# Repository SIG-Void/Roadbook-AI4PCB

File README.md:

<h1 align="center"> Roadbook AI4PCB</h1>

Hardware engineers and researchers at SIGVoid maintain Roadbook AI4PCB. We study which parts of printed circuit board (PCB) design engineers can already hand over to AI. Here you can read research papers and engineering notes, or open a board file to see which connections a model got right. We are testing how well models read circuit diagrams, place parts, and connect them. We are also building training datasets from the steps engineers take to design a board and the checks they use to verify it.

<p align="center"><strong>English</strong> · <a href="README.zh-CN.md">中文</a> &nbsp; | &nbsp; <a href="https://sig-void.github.io/Roadbook-AI4PCB/">Explore the full roadbook ↗</a></p>

[Selected papers](#read-papers) · [Benchmarks and submissions](#read-benchmarks) · [Run a Harbor example](#read-harbor) · [Data and weights](#read-data) · [PCB engineering notes](#read-boards) · [Contribute](#read-contribute)

## Where can AI help with PCB design?

A schematic specifies which pins belong together. Placement sets the positions of the components. Routing adds the copper that connects their pads. Each paper below produces a different artifact you can inspect.

| Engineering question | Paper and project | What to inspect |
| --- | --- | --- |
| Can a model recover connections from a drawing? | [OmniSch paper](https://arxiv.org/abs/2604.00270) · [Examples and data](https://www.omnisch.com/) | Locate components and wires in a schematic. Compare the extracted connections with the netlist, which records which pins belong together. |
| Can a model draw an editable schematic from a requirement? | [SchGen paper](https://arxiv.org/abs/2605.30345) · [Code and examples](https://github.com/microsoft/SchGen) | Follow a 3.3 V regulator example from a written requirement to a KiCad schematic. Check the power pins in the result. |
| Will a proposed placement leave room for routing? | [RL_PCB paper](https://past.date-conference.com/proceedings-archive/2024/DATA/1040_pdf_upload.pdf) · [Test circuits](https://github.com/LukeVassallo/RL_PCB) | The model moves components. A router connects the resulting layout so the authors can compare placements by actual trace length. |
| Can an agent finish routing a board? | [PCBWorld environment](https://github.com/LGAI-Research/PCBWorld) · [PCBRouteAgent paper](https://arxiv.org/abs/2611.08175) | Starting from a placed board, the agent chooses the routing order and where to change layers. Inspect the final board in KiCad. |
| Can a model learn from routing actions? | [CADET paper](https://arxiv.org/abs/2611.16913) · [Generation and replay code](https://github.com/LGAI-Research/CADET) | Generate routing demonstrations, replay them in a fresh environment, and compare imitation learning with reinforcement learning. |

[Browse all papers by design stage →](https://sig-void.github.io/Roadbook-AI4PCB/research/papers/)

## Benchmarks and model submissions

**Agents’ Last Exam (ALE)** includes two KiCad tasks. The layout task starts with a schematic and asks for a routed board that fits a specified enclosure. The repair task asks the model to restore the footprint for U4 on a navigation switch board and export the manufacturing files.

SIGVoid ran each model once on each task in the ALE v1.1 Windows environment. The maximum score is 1 per task. Each ZIP contains the submitted files, a step-by-step action log, and the score.

| Model and reasoning setting | Board layout and routing | Navigation switch repair |
| --- | --- | --- |
| DeepSeek V4.1 Flash · max | **1** · [Submission and actions](https://sig-void.github.io/Roadbook-AI4PCB/assets/runs/ale-mini-deepseek.zip) | **0** · [Submission and actions](https://sig-void.github.io/Roadbook-AI4PCB/assets/runs/ale-navswitch-deepseek.zip) |
| Qwen4-Max-Preview · xhigh | **0** · [Submission and actions](https://sig-void.github.io/Roadbook-AI4PCB/assets/runs/ale-mini-qwen4.zip) | **0** · [Submission and actions](https://sig-void.github.io/Roadbook-AI4PCB/assets/runs/ale-navswitch-qwen4.zip) |

<p align="center"><br><sub>The DeepSeek layout submission, rendered from its KiCad file. Select the board to open the source.</sub></p>

Why did both repair submissions score zero? Both models fixed U4. DeepSeek omitted the required report formats and netlist. Qwen used different export names and omitted the required drill directory. Both submissions failed the required-file check. [Inspect the requirements and results](https://sig-void.github.io/Roadbook-AI4PCB/research/benchmarks/#ale-navswitch)

**What do the other benchmarks measure?**

- **OmniLayout tests placement.** A model supplies component positions, rotations, and board sides. The evaluator checks overlaps and boundaries, then tries to route the board. GPT-5.5 passed 15.23% of cases on its first submission with the base input and 42.83% with an added schematic. [Paper, Table 2](https://arxiv.org/html/2607.03261v3#S5.T2)
- **BenchCAD T6 tests connection recovery from board images.** Models can use offline Python to inspect the views. They submit component terminals and their nets. On the 12 boards in 2.0 Core T6, GPT-6 Astra averaged 0.4222 under the corrected rule. Claude Opus 5.5 averaged 0.3983. SIGVoid evaluated a separate set of nine Public practice boards. [Official results and scoring notes](https://sig-void.github.io/Roadbook-AI4PCB/research/benchmarks/#benchcad-t6) · [Per-case action traces (CSV)](https://sig-void.github.io/Roadbook-AI4PCB/assets/runs/benchcad-public-t6-traces.csv) · [Batch scores (CSV)](https://sig-void.github.io/Roadbook-AI4PCB/assets/runs/benchcad-public-t6.csv)

## Score a board with Harbor

The Harbor package includes the ALE input schematic, a model submission, and the original scoring program. You can open the [task](assets/harbor/ale-mini-encabulator/instruction.md), [schematic](assets/harbor/ale-mini-encabulator/environment/input/mini_encabulator.kicad_sch), and [routed board](assets/harbor/ale-mini-encabulator/solution/sample/mini_encabulator.kicad_pcb) directly in this repository.

Install Harbor 0.25.0 and start Docker with Linux AMD64 container support. Run these commands from the repository root.

```sh
harbor run -p ./assets/harbor/ale-mini-encabulator -a oracle
harbor run -p ./assets/harbor/ale-mini-encabulator -a nop
```

The first command replays the submitted board. Its expected score is **1**. The second submits an empty directory. Its expected score is **0**. For each trial, open `verifier/checks.json` for individual checks and `verifier/reward.txt` for the score. [Browse the task files](https://sig-void.github.io/Roadbook-AI4PCB/research/harbor-examples/) · [Setup and scoring details](assets/harbor/ale-mini-encabulator/README.md)

## Data, models, and reproducible experiments

- **Original board files.** The PCBench buck regulator sample includes the original board, a cleaned version, and routing data in JSON. Select a pad on the original board and compare its net and traces with the JSON. [Sample directory](https://github.com/PCBench/PCBench/tree/dec3be75cbdef74787625f9043c7391cd473bb64/PCBs/C-BISCUIT_buck-reg-5v) · [Check the quality of a board file](https://sig-void.github.io/Roadbook-AI4PCB/research/datasets/procurement/)
- **Downloadable weights.** SchGen publishes an adapter for schematic generation. Micius-Flash provides multimodal engineering model weights and a KiCad case study. CADET publishes routing policies trained by imitation and by subsequent reinforcement learning. [SchGen adapter](https://huggingface.co/microsoft/SchGen) · [Micius-Flash weights](https://huggingface.co/zhiman-ai/Micius-Flash) · [CADET policies](https://huggingface.co/LG-AI-Research/CADET)
- **A CPU experiment.** Fit a model on 112 reference boards to predict net count from board area. On 29 held-out boards, the mean absolute error was 5.72 nets. Always predicting the training median gave an error of 6.00 nets. The guide includes the data, Python script, and expected output. [Reproduce the experiment](https://sig-void.github.io/Roadbook-AI4PCB/research/training/)

[Browse datasets](https://sig-void.github.io/Roadbook-AI4PCB/research/datasets/) · [Models and weights](https://sig-void.github.io/Roadbook-AI4PCB/research/models/) · [KiCad agents and plugins](https://sig-void.github.io/Roadbook-AI4PCB/research/agents/)

## From schematic to fabrication files

<p align="center"></p>

For a first board, follow a SIGVoid hardware engineer’s [PCB design notes](https://sig-void.github.io/Roadbook-AI4PCB/workflow/). For an existing design, use the [tool guide](https://sig-void.github.io/Roadbook-AI4PCB/design/tools/) to find the file types and export settings. The [design review](https://sig-void.github.io/Roadbook-AI4PCB/design/review/) covers footprints, drilling, and assembly files.

| Engineering question | What the files show |
| --- | --- |
| [Do the mounting holes match the enclosure after the design checks pass?](https://sig-void.github.io/Roadbook-AI4PCB/blog/design-checks/) | Measure the hole centers in two drill files. Moving one hole by 1 mm changes the spacing from 30 mm to 29 mm. Both designs pass the rule checks. |
| [Why does a capacitor’s placement coordinate change sign?](https://sig-void.github.io/Roadbook-AI4PCB/blog/assembly-origin/) | Export the same Cynthion board with a different origin, then mirror the bottom-side X coordinates. Use a top-side component as a control. |
| [Do pads on the same net have a copper connection?](https://sig-void.github.io/Roadbook-AI4PCB/blog/rp2040-power/) | Remove a short trace from a copy of an RP2040 board. The pads keep the same net name, and KiCad can locate the break. |
| [Why does a voltage reading change under interference?](https://sig-void.github.io/Roadbook-AI4PCB/blog/revision-task/) | Read the Glasgow frequency sweep and inspect the board revision. See why the engineers changed a series resistor and fitted an input capacitor. |
| [At 94.9% average routing completion, how many boards passed?](https://sig-void.github.io/Roadbook-AI4PCB/blog/routing-scores/) | In a ten-board test, four had every connection complete and zero error-level violations. Follow the paper’s tables to reproduce both measures. |
| [Does a revised board give a model an independent test?](https://sig-void.github.io/Roadbook-AI4PCB/blog/board-family-split/) | Two OLIMEX revisions differ by one resistor but export the same 142 placement rows. Compare the changed component with the fields used for scoring. |

[Open reference board projects](https://sig-void.github.io/Roadbook-AI4PCB/design/boards/) · [Read all engineering notes](https://sig-void.github.io/Roadbook-AI4PCB/blog/)

## Contribute and collaborate

Share a PCB paper, editable board design, dataset, or runnable environment. Include the original link and tell readers which file to open and what they can check. [Open a pull request](https://github.com/SIG-Void/Roadbook-AI4PCB/compare) · [Suggest a resource](https://github.com/SIG-Void/Roadbook-AI4PCB/issues) · [View contributors](https://github.com/SIG-Void/Roadbook-AI4PCB/graphs/contributors)

PCB specialists can help define benchmark tasks and review model submissions. Hardware and model teams can work with SIGVoid on PCB design capabilities or commission task-specific training data. [Partnerships and contact](https://sig-void.github.io/Roadbook-AI4PCB/about/#collaborate)

<details>
<summary>Build and check the site locally</summary>

Use Python 3.11 or later. Run these commands from the repository root.

```sh
python3 -m venv .venv
.venv/bin/python -m pip install -r requirements.txt
.venv/bin/python scripts/build.py
.venv/bin/python scripts/check_site.py
.venv/bin/python -m http.server 8765 --bind 127.0.0.1 --directory dist
```

Open [localhost:8765](http://127.0.0.1:8765/). The bilingual articles live in [content](content/). [scripts/build.py](scripts/build.py) defines the navigation. Each merge into `main` triggers a [Pages build](https://github.com/SIG-Void/Roadbook-AI4PCB/actions/workflows/pages.yml).

</details>

<details>
<summary>Sources and design credits</summary>

The directory layout draws on [Awesome AI4Chip](https://github.com/tapeo-ai/awesome-ai4chip). Some paper and plugin leads came from the [engineering agents directory](https://github.com/whut09/Awesome-AI-Engineering-Agents), which uses the [MIT license](https://github.com/whut09/Awesome-AI-Engineering-Agents/blob/main/LICENSE). Each linked project has its own license. The website uses [IBM Carbon colors](https://carbondesignsystem.com/elements/color/overview/). Font licenses are in [assets/fonts](assets/fonts/).

</details>

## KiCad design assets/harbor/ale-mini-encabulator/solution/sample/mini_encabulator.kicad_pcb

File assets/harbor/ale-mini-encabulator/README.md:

# Mini Encabulator PCB layout

This package adapts the [Agents’ Last Exam v1.1 task](https://github.com/rdi-berkeley/agents-last-exam/tree/2e91edd3cd26baa35a38127c90c8e5241dfbe62f/tasks/engineering/pcb_layout_kicad_1) for Harbor. The official task uses a Windows desktop. This example runs KiCad 10.0.0 command-line tools in Linux containers.

## Run the verifier

Install Harbor 0.25.0. Start Docker with Linux AMD64 containers or AMD64 emulation. Extract the ZIP. Run each command from the directory that contains `ale-mini-encabulator/`.

```sh
harbor run -p ./ale-mini-encabulator -a oracle
harbor run -p ./ale-mini-encabulator -a nop
```

The first command replays the published DeepSeek V4.1 Flash submission from SIGVoid’s ALE run. The second submits an empty output directory. Each trial saves `reward.txt` and `checks.json` under `verifier/`. A completed KiCad check also produces `drc.json`.

## Inspect a design

Open `environment/input/mini_encabulator.kicad_sch` in desktop KiCad to inspect the circuit and footprint assignments. Open `solution/sample/mini_encabulator.kicad_pcb` to inspect the submitted layout. To score your own board, replace the sample in an extracted copy and run the first command again.

The agent and verifier use separate containers. Only the submitted board crosses the boundary. The verifier copies it to a clean directory, runs KiCad DRC, and passes the resulting JSON and board text to the original ALE scorer.

| Score | Condition |
| --- | --- |
| 1 | DRC reports zero violations and zero unconnected items. All structural checks pass. |
| 0.5 | DRC passes. At least one structural check fails. |
| 0 | The board is missing, DRC is unavailable, or DRC reports violations or unconnected items. |

The command-line replay checks a submitted artifact. ALE leaderboard runs also include the original agent and Windows environment.

## Files and attribution

| Path | Origin |
| --- | --- |
| `upstream/task_card.json` | ALE task card, including the original Windows instructions |
| `environment/input/mini_encabulator.kicad_sch` | Published ALE v1.1 input schematic |
| `tests/score_outputs.py` | Original ALE scorer, unchanged |
| `solution/sample/mini_encabulator.kicad_pcb` | Model submission from SIGVoid’s published run |
| `tests/verify.py` and the Dockerfiles | Roadbook’s Harbor integration |

UC Berkeley RDI and RDI Foundation released the benchmark data under [CC BY 4.0](https://creativecommons.org/licenses/by/4.0/). Roadbook adapted paths and runtime instructions. The upstream license texts are in `licenses/`.

[Original task and scorer](https://github.com/rdi-berkeley/agents-last-exam/tree/2e91edd3cd26baa35a38127c90c8e5241dfbe62f/tasks/engineering/pcb_layout_kicad_1) · [Original input schematic](https://huggingface.co/datasets/agents-last-exam/agents-last-exam-data/blob/e9a2674a62f7d8069f136e642c10e8d8e9979dbf/tasks/engineering/pcb_layout_kicad_1/base/input/mini_encabulator.kicad_sch) · [Published model submission and action trace](https://sig-void.github.io/Roadbook-AI4PCB/assets/runs/ale-mini-deepseek.zip)

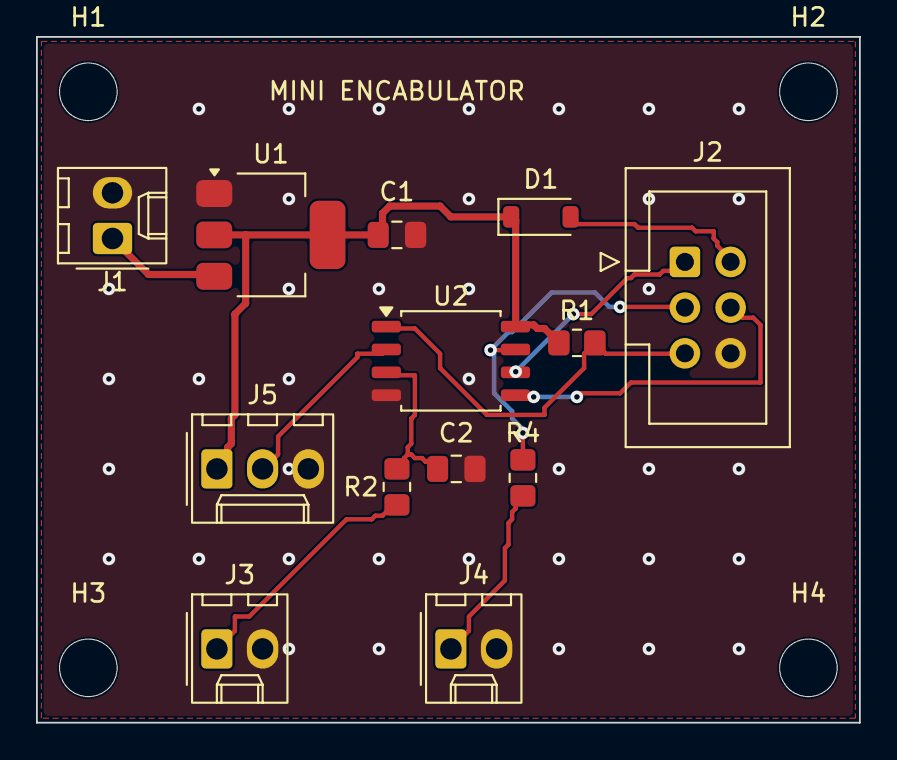
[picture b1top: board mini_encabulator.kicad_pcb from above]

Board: 2 copper layers, 45.7 x 38.1 mm, 17 parts (0 on the bottom side), 12 nets.

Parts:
C1, C2: 1uF; C_0805_2012Metric_Pad1.18x1.45mm_HandSolder
D1: MBR0520; D_SOD-123
H1, H2, H3, H4: MountingHole; MountingHole_3.2mm_M3
J1: Vin; Molex_KK-254_AE-6410-02A_1x02_P2.54mm_Vertical
J2: ISP; IDC-Header_2x03_P2.54mm_Vertical
J3: BUTTON; Molex_KK-254_AE-6410-02A_1x02_P2.54mm_Vertical
J4: LED; Molex_KK-254_AE-6410-02A_1x02_P2.54mm_Vertical
J5: POT; Molex_KK-254_AE-6410-03A_1x03_P2.54mm_Vertical
R1, R2: 10k; R_0805_2012Metric_Pad1.20x1.40mm_HandSolder
R4: 1k; R_0805_2012Metric_Pad1.20x1.40mm_HandSolder
U1: LM1117MP-5.0; SOT-223-3_TabPin2
U2: ATtiny85-20S; SOIC-8_5.3x5.3mm_P1.27mm

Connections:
+5V: C1.1, D1.1, J5.1, R1.1, U1.2, U2.8
/BUTTON: C2.1, R2.2, U2.3
/MISO: J2.1, U2.6
/MOSI: J2.4, U2.5
/RST: J2.5, R1.2, U2.1
/SCK: J2.3, R4.2, U2.7
GND: C1.2, C2.2, J1.2, J2.6, J3.2, J4.2, J5.3, U1.1, U2.4
unnamed: D1.2, J2.2
unnamed: J1.1, U1.3
unnamed: J3.1, R2.1
unnamed: J4.1, R4.1
unnamed: J5.2, U2.2
